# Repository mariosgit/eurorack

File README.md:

# Changes by mariosgit..

in branch mb/402to603
* Marbles 402->603
* Paits 402->603

in branch master
* Stages, fixed LED resistor 15k -> 150ohm
* Grids changed plug footprint

# Mutable Instruments' Eurorack Modules.

* [Blades](http://mutable-instruments.net/modules/blades): Dual multimode filter.
* [Blinds](http://mutable-instruments.net/modules/blinds): Quad VC-polarizer.
* [Braids](http://mutable-instruments.net/modules/braids): Macro-oscillator.
* [Branches](http://mutable-instruments.net/modules/branches): Dual Bernoulli gate.
* [Clouds](http://mutable-instruments.net/modules/clouds): Texture synthesizer.
* [Ears](http://mutable-instruments.net/modules/ears): Contact microphone.
* [Edges](http://mutable-instruments.net/modules/edges): Quad chiptune digital oscillator.
* [Elements](http://mutable-instruments.net/modules/elements): Modal synthesizer.
* [Frames](http://mutable-instruments.net/modules/frames): Keyframer/mixer.
* [Grids](http://mutable-instruments.net/modules/grids): Topographic drum sequencer.
* [Kinks](http://mutable-instruments.net/modules/kinks): Utility module - rectifier, analog logic, S&H, noise.
* [Links](http://mutable-instruments.net/modules/links): Utility module - buffer, mixer.
* [Marbles](http://mutable-instruments.net/modules/marbles): Random sampler.
* [Peaks](http://mutable-instruments.net/modules/peaks): Dual trigger converter.
* [Plaits](http://mutable-instruments.net/modules/plaits): Macro oscillator.
* [Rings](http://mutable-instruments.net/modules/rings): Resonator.
* [Ripples](http://mutable-instruments.net/modules/ripples): Liquid 2-pole BP, 2-pole LP and 4-pole LP filter.
* [Shades](http://mutable-instruments.net/modules/shades): Triple attenuverter.
* [Shelves](http://mutable-instruments.net/modules/shelves): EQ filter.
* [Stages](http://mutable-instruments.net/modules/stages): Segment generator.
* [Streams](http://mutable-instruments.net/modules/streams): Dual dynamics gate.
* [Tides](http://mutable-instruments.net/modules/tides): Tidal modulator.
* [Veils](http://mutable-instruments.net/modules/veils): Quad VCA.
* [Volts](http://mutable-instruments.net/modules/volts): +5V power module.
* [Warps](http://mutable-instruments.net/modules/warps): Meta-modulator.
* [Yarns](http://mutable-instruments.net/modules/yarns): MIDI interface.

License
=======

Code (AVR projects): GPL3.0.

Code (STM32F projects): MIT license.

Hardware: cc-by-sa-3.0

By: Emilie Gillet (emilie.o.gillet@gmail.com)

Guidelines for derivative works
===============================

**Mutable Instruments is a registered trademark.**

The name "Mutable Instruments" should not be used on any of the derivative works you create from these files.

We do not recommend you to keep the original name of the Mutable Instruments module for your derivative works.

For example, your 5U adaptation of Mutable Instruments Clouds can be called "Foobar Modular - Particle Generator".

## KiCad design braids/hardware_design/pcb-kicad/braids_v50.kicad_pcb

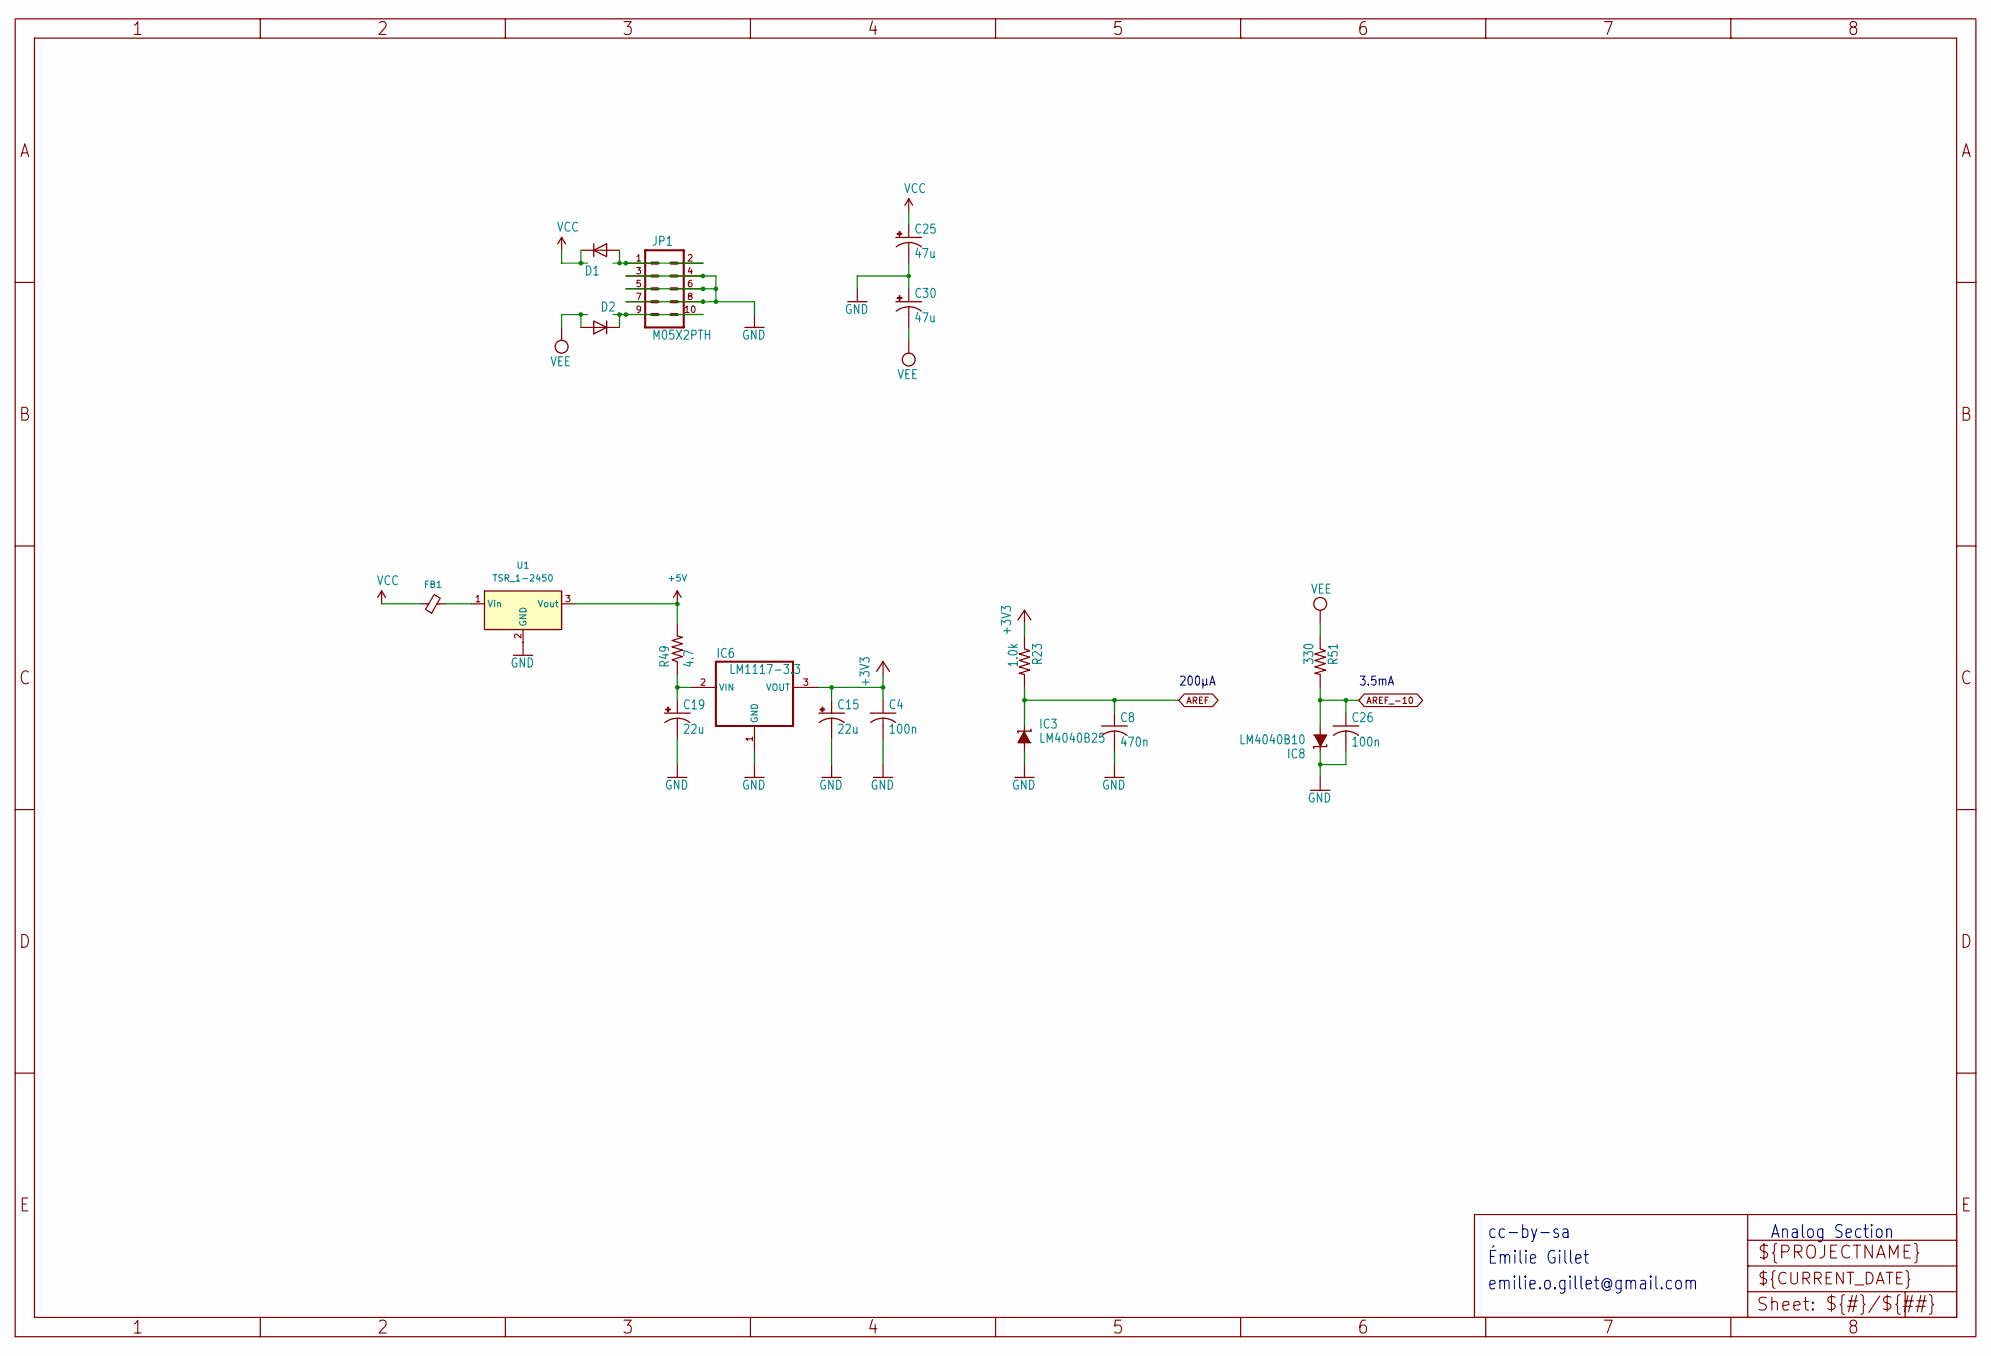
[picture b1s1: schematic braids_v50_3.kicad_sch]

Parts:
C4, C26: 100n; C0603
C8: 470n; C0603
C15, C19: 22u; PANASONIC_C
C25, C30: 47u; PANASONIC_D
D1, D2: 1N5819HW; Nexperia_CFP3_SOD-123W
FB1: FerriteBead_Small
IC3: LM4040B25; DBZ_R-PDSO-G3
IC6: LM1117-3.3; TO252
IC8: LM4040B10; DBZ_R-PDSO-G3
JP1: M05X2PTH; AVR_ICSP
R23: 1.0k; R0603
R49: 4.7; R1206
R51: 330; R0603
U1: TSR_1-2450; Converter_DCDC_TRACO_TSR-1_THT

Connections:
+3V3: C4.1, C15.+, IC6.3 (VOUT), R23.1; also elsewhere on the board
+5V: R49.2, U1.3 (Vout)
AREF: C8.1, IC3.1 (C), R23.2; also elsewhere on the board
AREF_-10: C26.1, IC8.2 (A), R51.2; also elsewhere on the board
GND: C4.2, C8.2, C15.-, C19.-, C25.-, C26.2, C30.+, IC3.2 (A), IC6.1 (GND), IC8.1 (C), JP1.3, JP1.4, JP1.5, JP1.6, JP1.7, JP1.8, U1.2 (GND); also elsewhere on the board
unnamed: D1.2 (A), JP1.1, JP1.2
unnamed: D2.1 (K), JP1.9, JP1.10
unnamed: C19.+, IC6.2 (VIN), R49.1
unnamed: FB1.2, U1.1 (Vin)
VCC: C25.+, D1.1 (K), FB1.1; also elsewhere on the board
VEE: C30.-, D2.2 (A), R51.1; also elsewhere on the board

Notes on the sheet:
Analog Section
3.5mA
Émilie Gillet
emilie.o.gillet@gmail.com
200µA
cc-by-sa

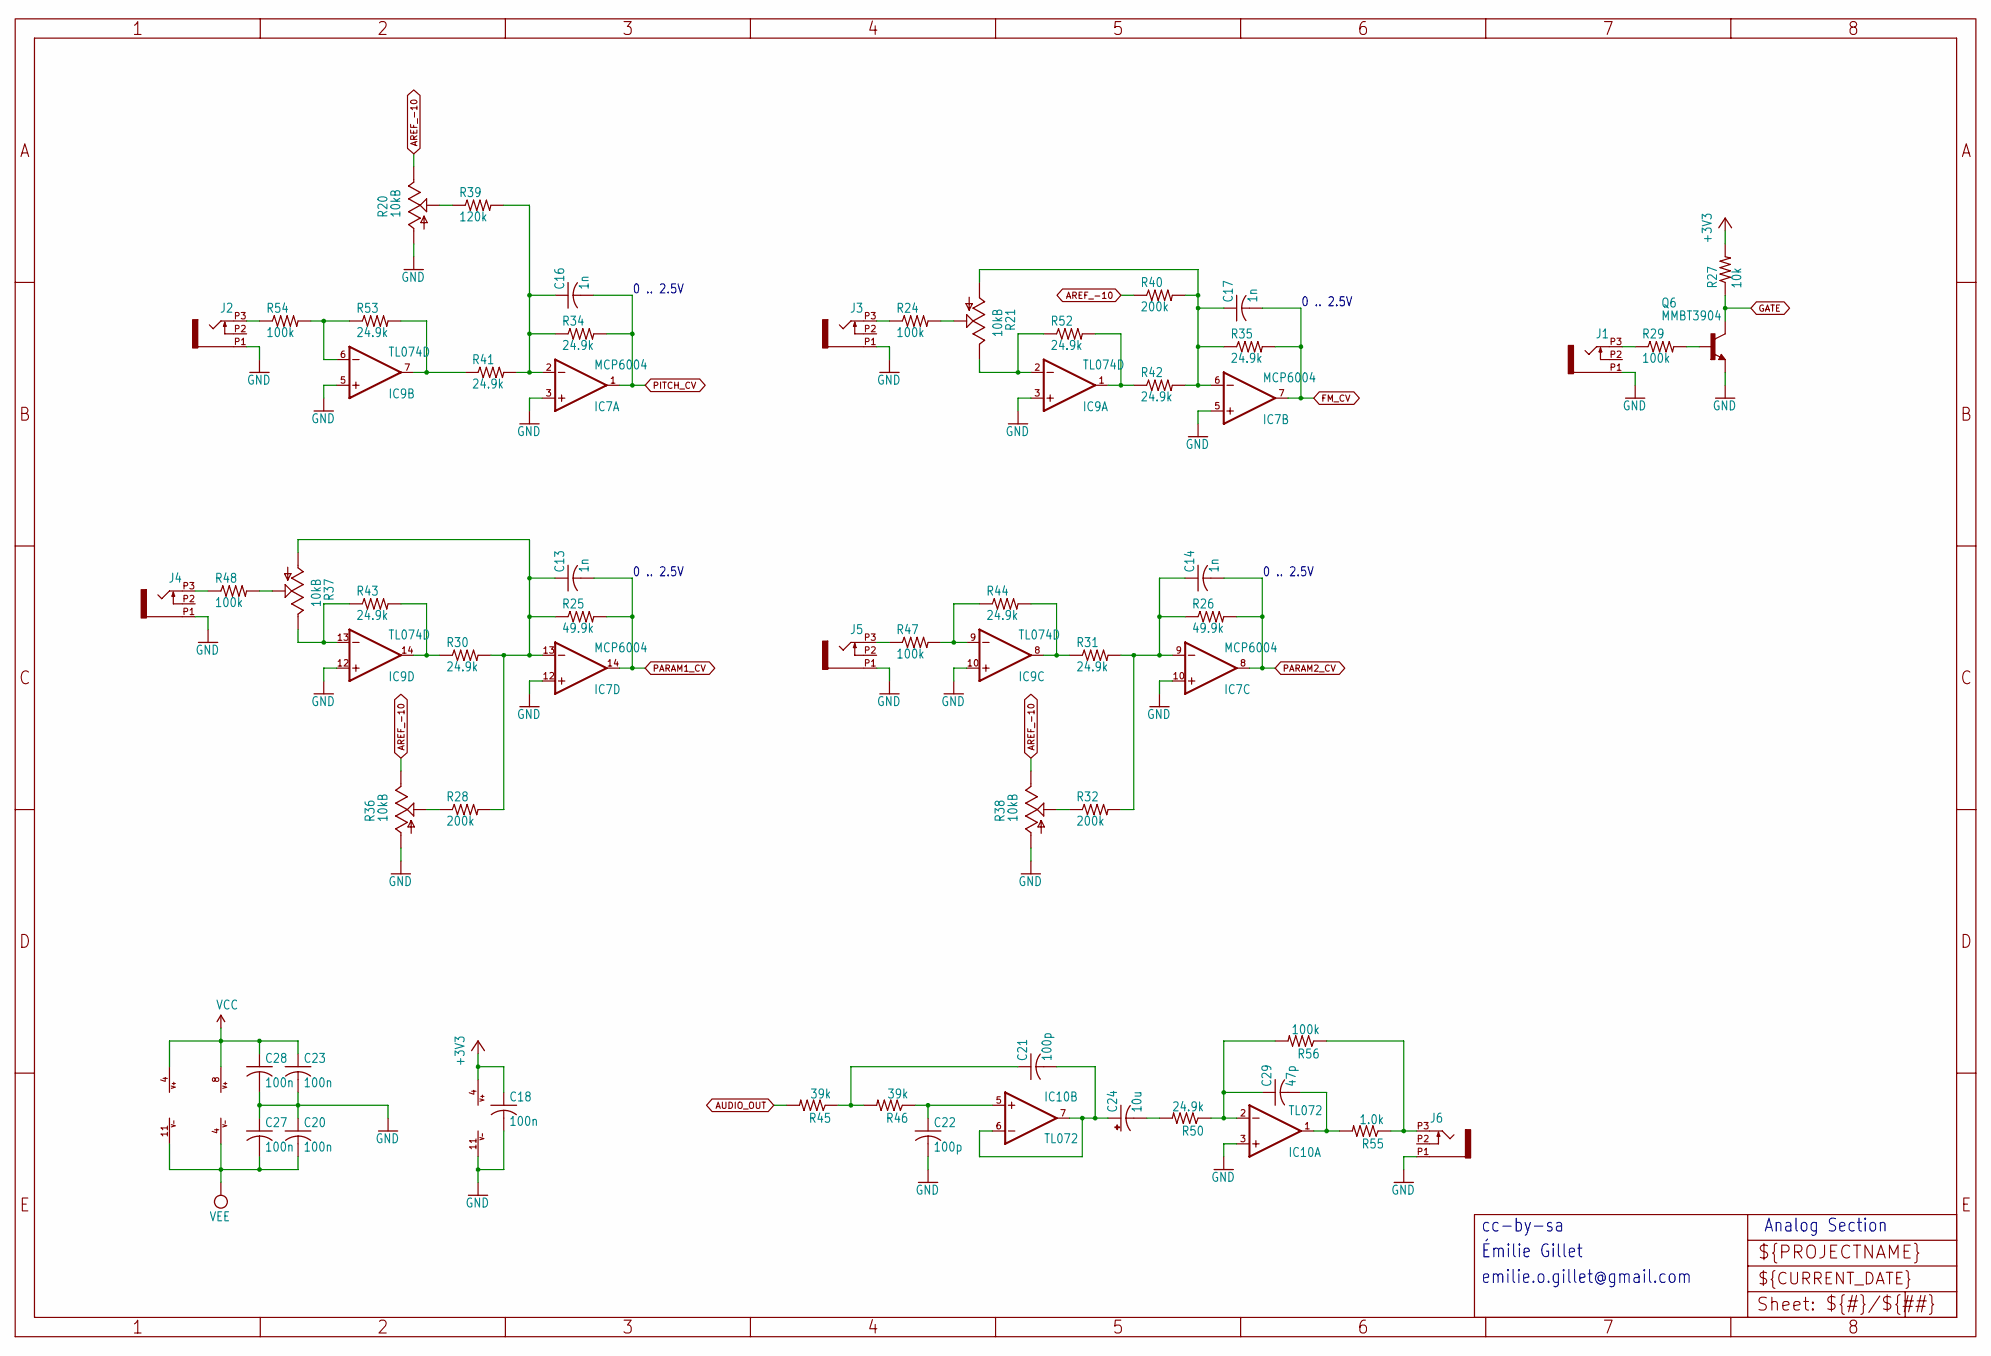
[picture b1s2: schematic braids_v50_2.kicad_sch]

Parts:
C13, C14, C16, C17: 1n; C0603
C18, C20, C23, C27, C28: 100n; C0603
C21, C22: 100p; C0603
C24: 10u; PANASONIC_B
C29: 47p; C0603
IC7: MCP6004; SO14
IC9: TL074D; SO14
IC10: TL072; SO08
J1, J2, J3, J4, J5, J6: PJ301_THONKICONN6; WQP_PJ_301M6
Q6: MMBT3904; SOT23-BEC
R20, R21, R36, R37, R38: 10kB; ALPS_POT_VERTICAL_PS
R24, R29, R47, R48, R54, R56: 100k; R0603
R25, R26: 49.9k; R0603
R27: 10k; R0603
R28, R32, R40: 200k; R0603
R30, R31, R34, R35, R41, R42, R43, R44, R50, R52, R53: 24.9k; R0603
R39: 120k; R0603
R45, R46: 39k; R0603
R55: 1.0k; R0603

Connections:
+3V3: C18.1, IC7.4 (V+), R27.2; also elsewhere on the board
AREF_-10: R20.P$1 (E), R36.P$1 (E), R38.P$1 (E), R40.1; also elsewhere on the board
AUDIO_OUT: R45.2; also elsewhere on the board
FM_CV: C17.2, IC7.7 (OUT), R35.2; also elsewhere on the board
GATE: Q6.C, R27.1; also elsewhere on the board
GND: C18.2, C20.1, C22.2, C23.2, C27.1, C28.2, IC7.3 (+IN), IC7.5 (+IN), IC7.10 (+IN), IC7.11 (V-), IC7.12 (+IN), IC9.3 (+IN), IC9.5 (+IN), IC9.10 (+IN), IC9.12 (+IN), IC10.3 (+IN), J1.P1 (1), J2.P1 (1), J3.P1 (1), J4.P1 (1), J5.P1 (1), J6.P1 (1), Q6.E, R20.P$3 (A), R36.P$3 (A), R38.P$3 (A); also elsewhere on the board
unnamed: C21.1, R45.1, R46.2
unnamed: C24.-, R50.2
unnamed: C16.1, IC7.2 (-IN), R34.1, R39.2, R41.2
unnamed: C17.1, IC7.6 (-IN), R21.P$3 (A), R35.1, R40.2, R42.2
unnamed: C14.1, IC7.9 (-IN), R26.1, R31.2, R32.2
unnamed: C13.1, IC7.13 (-IN), R25.1, R28.2, R30.2, R37.P$3 (A)
unnamed: IC9.2 (-IN), R21.P$1 (E), R52.1
unnamed: IC9.1 (OUT), R42.1, R52.2
unnamed: IC9.6 (-IN), R53.1, R54.2
unnamed: IC9.7 (OUT), R41.1, R53.2
unnamed: IC9.9 (-IN), R44.1, R47.2
unnamed: IC9.8 (OUT), R31.1, R44.2
unnamed: IC9.13 (-IN), R37.P$1 (E), R43.1
unnamed: IC9.14 (OUT), R30.1, R43.2
unnamed: C29.1, IC10.2 (-IN), R50.1, R56.2
unnamed: C29.2, IC10.1 (OUT), R55.2
unnamed: C22.1, IC10.5 (+IN), R46.1
unnamed: C21.2, C24.+, IC10.6 (-IN), IC10.7 (OUT)
unnamed: J1.P3 (3), R29.1
unnamed: J2.P3 (3), R54.1
unnamed: J3.P3 (3), R24.1
unnamed: J4.P3 (3), R48.1
unnamed: J5.P3 (3), R47.1
unnamed: J6.P3 (3), R55.1, R56.1
unnamed: Q6.B, R29.2
unnamed: R20.P$2 (S), R39.1
unnamed: R21.P$2 (S), R24.2
unnamed: R28.1, R36.P$2 (S)
unnamed: R37.P$2 (S), R48.2
unnamed: R32.1, R38.P$2 (S)
PARAM1_CV: C13.2, IC7.14 (OUT), R25.2; also elsewhere on the board
PARAM2_CV: C14.2, IC7.8 (OUT), R26.2; also elsewhere on the board
PITCH_CV: C16.2, IC7.1 (OUT), R34.2; also elsewhere on the board
VCC: C23.1, C28.1, IC9.4 (V+), IC10.8 (V+); also elsewhere on the board
VEE: C20.2, C27.2, IC9.11 (V-), IC10.4 (V-); also elsewhere on the board

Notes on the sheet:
cc-by-sa
0 .. 2.5V
Émilie Gillet
Analog Section
emilie.o.gillet@gmail.com

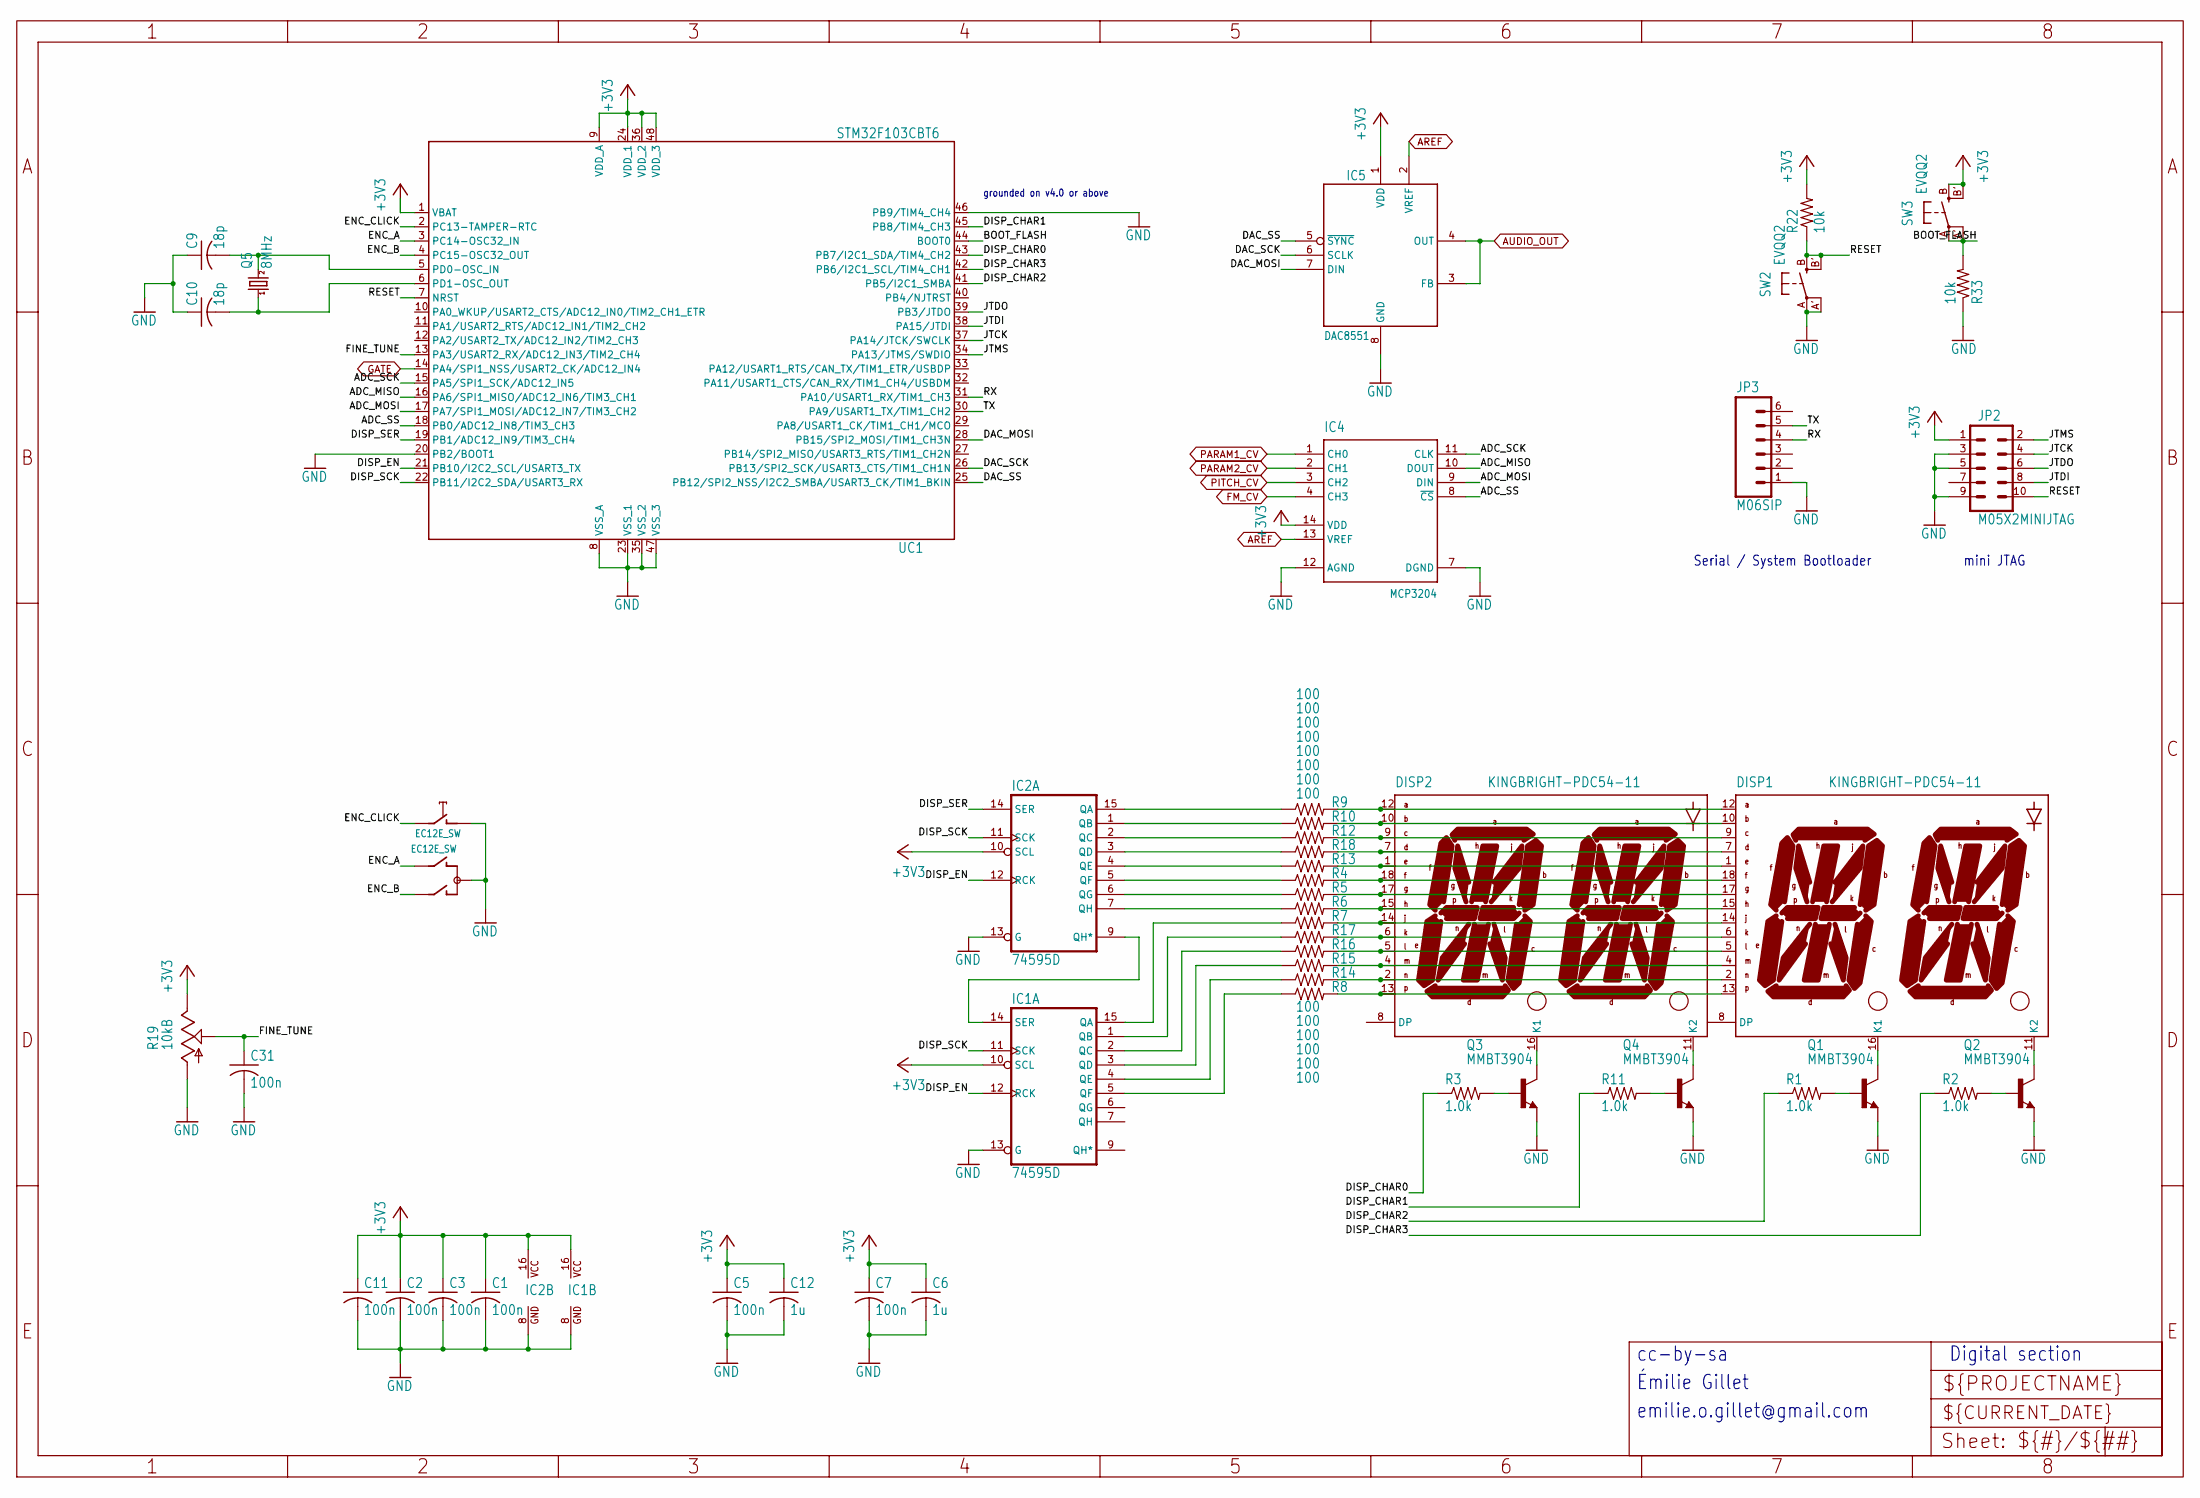
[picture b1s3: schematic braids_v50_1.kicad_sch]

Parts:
C1, C2, C3, C5, C7, C11, C31: 100n; C0603
C6, C12: 1u; C0603
C9, C10: 18p; C0603
DISP1, DISP2: KINGBRIGHT-PDC54-11; PDC54
IC1, IC2: 74595D; SO16
IC4: MCP3204; SO14
IC5: DAC8551; MSOP-8
JP2: M05X2MINIJTAG; 2X5-1.27
JP3: M06SIP; 1X06
Q1, Q2, Q3, Q4: MMBT3904; SOT23-BEC
Q5: 8MHz; HC49UP
R1, R2, R3, R11: 1.0k; R0603
R4, R5, R6, R7, R8, R9, R10, R12, R13, R14, R15, R16, R17, R18: 100; R0603
R19: 10kB; ALPS_POT_VERTICAL_PS
R22, R33: 10k; R0603
SW1: EC12E_SW; ALPS_EC12E_SW
SW2, SW3: EVQQ2; EVQ-Q2
UC1: STM32F103CBT6; LQFP48

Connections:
+3V3: C1.1, C2.1, C3.1, C5.1, C6.1, C7.1, C11.1, C12.1, IC1.10 (SCL), IC1.16 (VCC), IC2.10 (SCL), IC2.16 (VCC), IC4.14 (VDD), IC5.1 (VDD), JP2.1, R19.P$1 (E), R22.2, SW3.B (S), SW3.B' (S1), UC1.1 (VBAT), UC1.9 (VDD_A), UC1.24 (VDD_1), UC1.36 (VDD_2), UC1.48 (VDD_3); also elsewhere on the board
/braids_v50_1/ADC_MISO: IC4.10 (DOUT), UC1.16 (PA6/SPI1_MISO/ADC12_IN6/TIM3_CH1)
/braids_v50_1/ADC_MOSI: IC4.9 (DIN), UC1.17 (PA7/SPI1_MOSI/ADC12_IN7/TIM3_CH2)
/braids_v50_1/ADC_SCK: IC4.11 (CLK), UC1.15 (PA5/SPI1_SCK/ADC12_IN5)
/braids_v50_1/ADC_SS: IC4.8 (~CS), UC1.18 (PB0/ADC12_IN8/TIM3_CH3)
/braids_v50_1/BOOT_FLASH: R33.2, SW3.A, SW3.A' (P1), UC1.44 (BOOT0)
/braids_v50_1/DAC_MOSI: IC5.7 (DIN), UC1.28 (PB15/SPI2_MOSI/TIM1_CH3N)
/braids_v50_1/DAC_SCK: IC5.6 (SCLK), UC1.26 (PB13/SPI2_SCK/USART3_CTS/TIM1_CH1N)
/braids_v50_1/DAC_SS: IC5.5 (~SYNC), UC1.25 (PB12/SPI2_NSS/I2C2_SMBA/USART3_CK/TIM1_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)
/braids_v50_1/DISP_CHAR0: R3.1, UC1.43 (PB7/I2C1_SDA/TIM4_CH2)
/braids_v50_1/DISP_CHAR1: R11.1, UC1.45 (PB8/TIM4_CH3)
/braids_v50_1/DISP_CHAR2: R1.1, UC1.41 (PB5/I2C1_SMBA)
/braids_v50_1/DISP_CHAR3: R2.1, UC1.42 (PB6/I2C1_SCL/TIM4_CH1)
/braids_v50_1/DISP_EN: IC1.12 (RCK), IC2.12 (RCK), UC1.21 (PB10/I2C2_SCL/USART3_TX)
/braids_v50_1/DISP_SCK: IC1.11 (SCK), IC2.11 (SCK), UC1.22 (PB11/I2C2_SDA/USART3_RX)
/braids_v50_1/DISP_SER: IC2.14 (SER), UC1.19 (PB1/ADC12_IN9/TIM3_CH4)
/braids_v50_1/ENC_A: SW1.B, UC1.3 (PC14-OSC32_IN)
/braids_v50_1/ENC_B: SW1.A, UC1.4 (PC15-OSC32_OUT)
/braids_v50_1/ENC_CLICK: SW1.E (2), UC1.2 (PC13-TAMPER-RTC)
/braids_v50_1/FINE_TUNE: C31.1, R19.P$2 (S), UC1.13 (PA3/USART2_RX/ADC12_IN3/TIM2_CH4)
/braids_v50_1/JTCK: JP2.4, UC1.37 (PA14/JTCK/SWCLK)
/braids_v50_1/JTDI: JP2.8, UC1.38 (PA15/JTDI)
/braids_v50_1/JTDO: JP2.6, UC1.39 (PB3/JTDO)
/braids_v50_1/JTMS: JP2.2, UC1.34 (PA13/JTMS/SWDIO)
/braids_v50_1/RESET: JP2.10, R22.1, SW2.B (S), SW2.B' (S1), UC1.7 (NRST)
/braids_v50_1/RX: JP3.4, UC1.31 (PA10/USART1_RX/TIM1_CH3)
/braids_v50_1/TX: JP3.5, UC1.30 (PA9/USART1_TX/TIM1_CH2)
AREF: IC4.13 (VREF), IC5.2 (VREF); also elsewhere on the board
AUDIO_OUT: IC5.3 (FB), IC5.4 (OUT); also elsewhere on the board
FM_CV: IC4.4 (CH3); also elsewhere on the board
GATE: UC1.14 (PA4/SPI1_NSS/USART2_CK/ADC12_IN4); also elsewhere on the board
GND: C1.2, C2.2, C3.2, C5.2, C6.2, C7.2, C9.1, C10.1, C11.2, C12.2, C31.2, IC1.8 (GND), IC1.13 (G), IC2.8 (GND), IC2.13 (G), IC4.7 (DGND), IC4.12 (AGND), IC5.8 (GND), JP2.3, JP2.5, JP2.9, JP3.1, Q1.E, Q2.E, Q3.E, Q4.E, R19.P$3 (A), R33.1, SW1.C, SW1.D (1), SW2.A, SW2.A' (P1), UC1.8 (VSS_A), UC1.20 (PB2/BOOT1), UC1.23 (VSS_1), UC1.35 (VSS_2), UC1.46 (PB9/TIM4_CH4), UC1.47 (VSS_3); also elsewhere on the board
unnamed: DISP1.12 (A), DISP2.12 (A), R9.2
unnamed: DISP1.10 (B), DISP2.10 (B), R10.2
unnamed: DISP1.9 (C), DISP2.9 (C), R12.2
unnamed: DISP1.7 (D), DISP2.7 (D), R18.2
unnamed: DISP1.1 (E), DISP2.1 (E), R13.2
unnamed: DISP1.18 (F), DISP2.18 (F), R4.2
unnamed: DISP1.17 (G), DISP2.17 (G), R5.2
unnamed: DISP1.15 (H), DISP2.15 (H), R6.2
unnamed: DISP1.14 (J), DISP2.14 (J), R7.2
unnamed: DISP1.16 (K1), Q1.C
unnamed: DISP1.11 (K2), Q2.C
unnamed: DISP1.6 (K), DISP2.6 (K), R17.2
unnamed: DISP1.5 (L), DISP2.5 (L), R16.2
unnamed: DISP1.4 (M), DISP2.4 (M), R15.2
unnamed: DISP1.2 (N), DISP2.2 (N), R14.2
unnamed: DISP1.13, DISP2.13, R8.2
unnamed: DISP2.16 (K1), Q3.C
unnamed: DISP2.11 (K2), Q4.C
unnamed: IC1.15 (QA), R7.1
unnamed: IC1.1 (QB), R17.1
unnamed: IC1.2 (QC), R16.1
unnamed: IC1.3 (QD), R15.1
unnamed: IC1.4 (QE), R14.1
unnamed: IC1.5 (QF), R8.1
unnamed: IC1.14 (SER), IC2.9 (QH*)
unnamed: IC2.15 (QA), R9.1
unnamed: IC2.1 (QB), R10.1
unnamed: IC2.2 (QC), R12.1
unnamed: IC2.3 (QD), R18.1
unnamed: IC2.4 (QE), R13.1
unnamed: IC2.5 (QF), R4.1
unnamed: IC2.6 (QG), R5.1
unnamed: IC2.7 (QH), R6.1
unnamed: Q1.B, R1.2
unnamed: Q2.B, R2.2
unnamed: Q3.B, R3.2
unnamed: Q4.B, R11.2
unnamed: C9.2, Q5.2, UC1.5 (PD0-OSC_IN)
unnamed: C10.2, Q5.1, UC1.6 (PD1-OSC_OUT)
PARAM1_CV: IC4.1 (CH0); also elsewhere on the board
PARAM2_CV: IC4.2 (CH1); also elsewhere on the board
PITCH_CV: IC4.3 (CH2); also elsewhere on the board

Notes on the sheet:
Digital section
mini JTAG
emilie.o.gillet@gmail.com
cc-by-sa
Serial / System Bootloader
Émilie Gillet
grounded on v4.0 or above

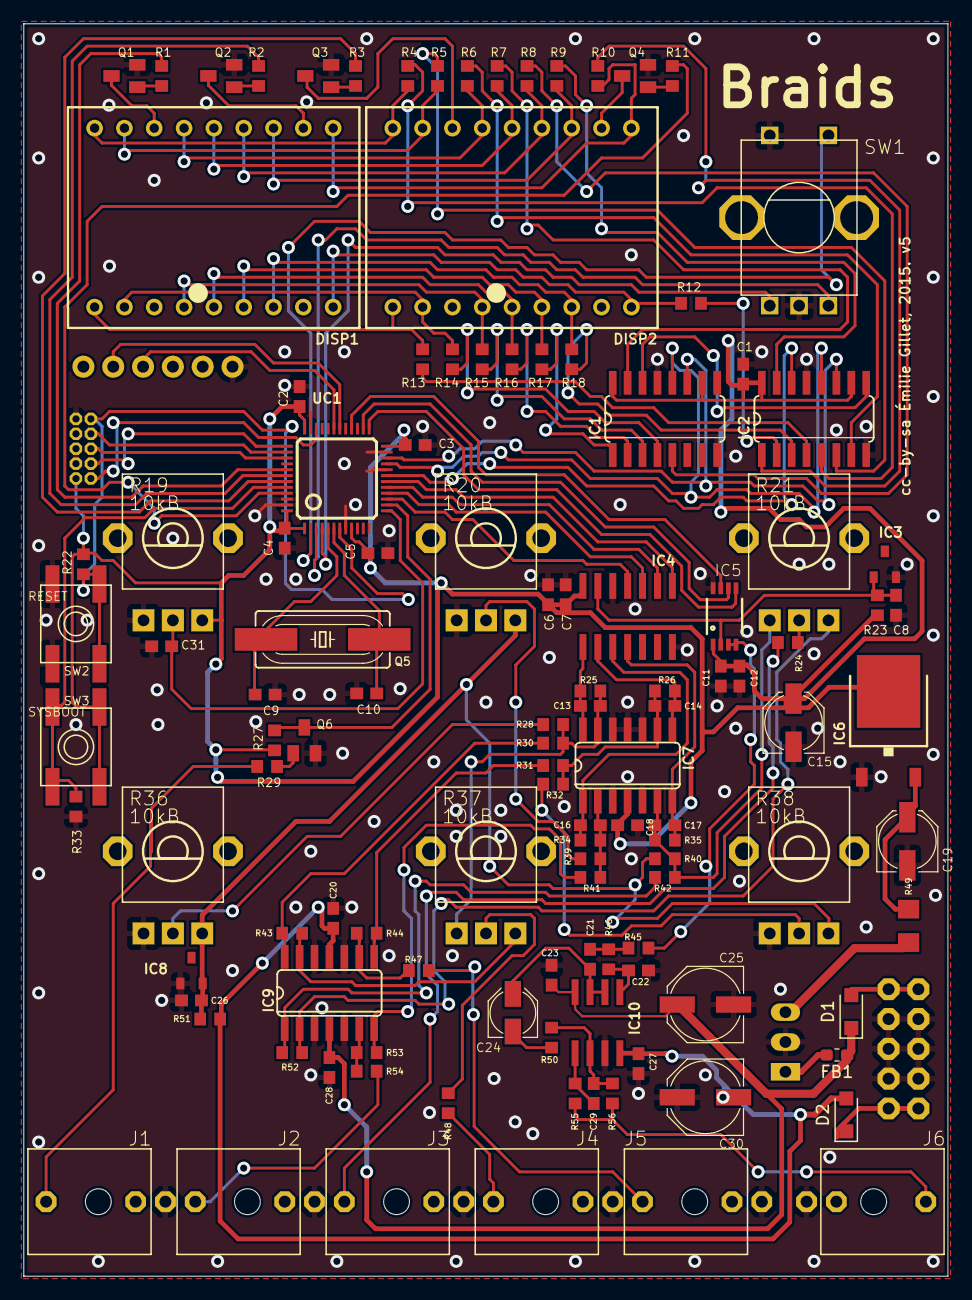
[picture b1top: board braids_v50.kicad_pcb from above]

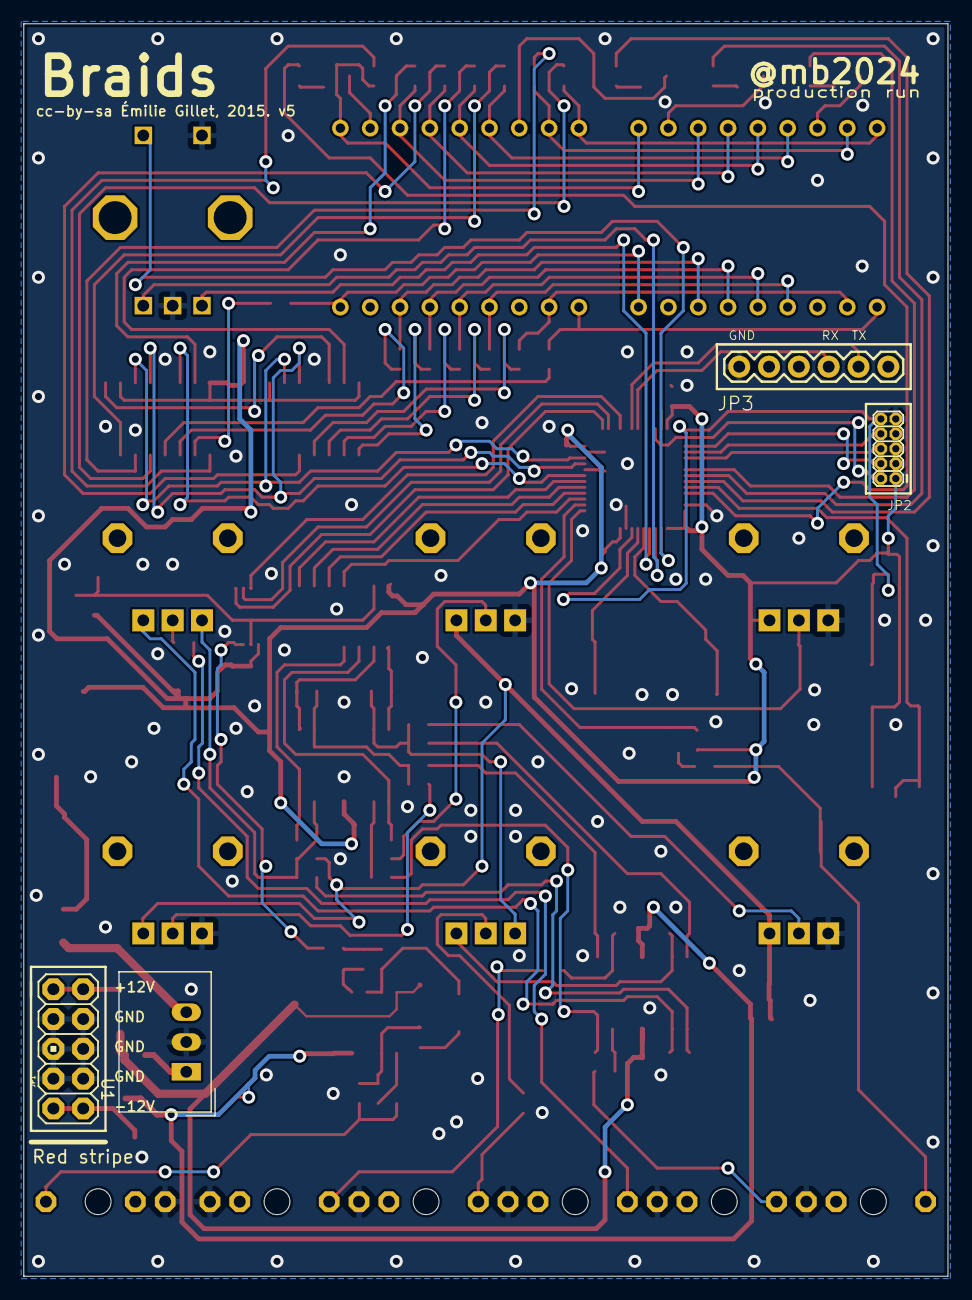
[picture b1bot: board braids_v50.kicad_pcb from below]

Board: 2 copper layers, 78.7 x 106.7 mm, 122 parts (4 on the bottom side), 112 nets.

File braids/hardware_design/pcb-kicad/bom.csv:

"Reference","Value","Datasheet","Footprint","Qty","DNP"
"C1,C2,C3,C4,C5,C7,C11,C18,C20,C23,C26,C27,C28,C31","100n","","braids_v50:C0603","14",""
"C6,C12","1u","","braids_v50:C0603","2",""
"C8","470n","","braids_v50:C0603","1",""
"C9,C10","18p","","braids_v50:C0603","2",""
"C13,C14,C16,C17","1n","","braids_v50:C0603","4",""
"C15,C19","22u","","braids_v50:PANASONIC_C","2",""
"C21,C22","100p","","braids_v50:C0603","2",""
"C24","10u","","braids_v50:PANASONIC_B","1",""
"C25,C30","47u","","braids_v50:PANASONIC_D","2",""
"C29","47p","","braids_v50:C0603","1",""
"D1,D2","1N5819HW","~","Diode_SMD:Nexperia_CFP3_SOD-123W","2",""
"DISP1,DISP2","KINGBRIGHT-PDC54-11","","braids_v50:PDC54","2",""
"FB1","FerriteBead_Small","~","","1",""
"IC1,IC2","74595D","","braids_v50:SO16","2",""
"IC3","LM4040B25","","braids_v50:DBZ_R-PDSO-G3","1",""
"IC4","MCP3204","","braids_v50:SO14","1",""
"IC5","DAC8551","","braids_v50:MSOP-8","1",""
"IC6","LM1117-3.3","","braids_v50:TO252","1",""
"IC7","MCP6004","","braids_v50:SO14","1",""
"IC8","LM4040B10","","braids_v50:DBZ_R-PDSO-G3","1",""
"IC9","TL074D","","braids_v50:SO14","1",""
"IC10","TL072","","braids_v50:SO08","1",""
"J1,J2,J3,J4,J5,J6","PJ301_THONKICONN6","","braids_v50:WQP_PJ_301M6","6",""
"JP1","M05X2PTH","","braids_v50:AVR_ICSP","1",""
"JP2","M05X2MINIJTAG","","braids_v50:2X5-1.27","1",""
"JP3","M06SIP","","braids_v50:1X06","1",""
"Q1,Q2,Q3,Q4,Q6","MMBT3904","","braids_v50:SOT23-BEC","5",""
"Q5","8MHz","","braids_v50:HC49UP","1",""
"R1,R2,R3,R11,R23,R55","1.0k","","braids_v50:R0603","6",""
"R4,R5,R6,R7,R8,R9,R10,R12,R13,R14,R15,R16,R17,R18","100","","braids_v50:R0603","14",""
"R19,R20,R21,R36,R37,R38","10kB","","braids_v50:ALPS_POT_VERTICAL_PS","6",""
"R22,R27,R33","10k","","braids_v50:R0603","3",""
"R24,R29,R47,R48,R54,R56","100k","","braids_v50:R0603","6",""
"R25,R26","49.9k","","braids_v50:R0603","2",""
"R28,R32,R40","200k","","braids_v50:R0603","3",""
"R30,R31,R34,R35,R41,R42,R43,R44,R50,R52,R53","24.9k","","braids_v50:R0603","11",""
"R39","120k","","braids_v50:R0603","1",""
"R45,R46","39k","","braids_v50:R0603","2",""
"R49","4.7","","braids_v50:R1206","1",""
"R51","330","","braids_v50:R0603","1",""
"SW1","EC12E_SW","","braids_v50:ALPS_EC12E_SW","1",""
"SW2,SW3","EVQQ2","","braids_v50:EVQ-Q2","2",""
"U1","TSR_1-2450","http://www.tracopower.com/products/tsr1.pdf","Converter_DCDC:Converter_DCDC_TRACO_TSR-1_THT","1",""
"UC1","STM32F103CBT6","","braids_v50:LQFP48","1",""

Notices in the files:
blades/hardware_design/pcb/blades_v41/blades_v40.kicad_pcb:
cc-by-sa É. Gillet
braids/hardware_design/pcb-kicad/braids_v50.kicad_pcb:
cc-by-sa Émilie Gillet, 2015. v5
edges/hardware_design/pcb/edges_v20/edges_v20.kicad_pcb:
cc-by-sa Émilie Gillet, 2014. v2
peaks/hardware_design/pcb/peaks_v30/peaks_v30.kicad_pcb:
cc-by-sa Émilie Gillet, 2015. v3
shelves/hardware_design/pcb/shelves_v60/shelves_v60.kicad_pcb:
cc-by-sa Émilie Gillet, 2014. v6
cc-by-sa Émilie Gillet, 2014. v0.6
streams/hardware_design/pcb/streams_v05/streams_v05.kicad_pcb:
cc-by-sa Émilie Gillet, 2014. v0.5
